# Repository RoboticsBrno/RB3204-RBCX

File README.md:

# RB3204-RBCX

<p align="center">

</p>

RBCX is a universal controller for hobby robots. It is a successor of [RB3201-RBControl](https://github.com/RoboticsBrno/RB3201-RBControl).
It is used in our robot [Robotka](https://robotka.robotickytabor.cz) on [Robo camp 2020](https://robotickytabor.cz).

<div align="center">
  	<td></td>
	<td></td>
</div>

## Features
- 4 DC motors with encoders
- 4 servos with feedback (via ADC)
- 4 LEDs
- buttons with the gamepad interface
- Smart Servo connector
- piezo buzzer
- RTC
- ultra-sonic distance sensor connector
- I2C connectors
- OLED display connector
- accelerometer and gyroscope
- micro USB and USB-C connectors
- battery connector (without charging circuit)

## Hardware
Board is based on `STM32F103VC` microcontroller and `ESP32-DevKitC`.

STM32 is used for motor control and other low-level tasks.
ESP32 is used for high-level tasks like communication with mobile app and sending commands to STM32 via UART.

### [STM32F103VC](https://www.st.com/en/microcontrollers-microprocessors/stm32f103vc.html)

-  72 MHz, 32bit ARM Cortex-M3
-  48 KiB RAM, 256 KiB Flash
-  5x UART, USB
-  Debug support (with ST-Link)
-  Programmable in C++, with FreeRTOS and stm32cube framework, in Platform.io
-  Our [bootloader](https://github.com/RoboticsBrno/sboot_stm32) based on [sboot_stm32](https://github.com/dmitrystu/sboot_stm32).

### [ESP32-DevKitC](https://www.espressif.com/en/products/devkits/esp32-devkitc)

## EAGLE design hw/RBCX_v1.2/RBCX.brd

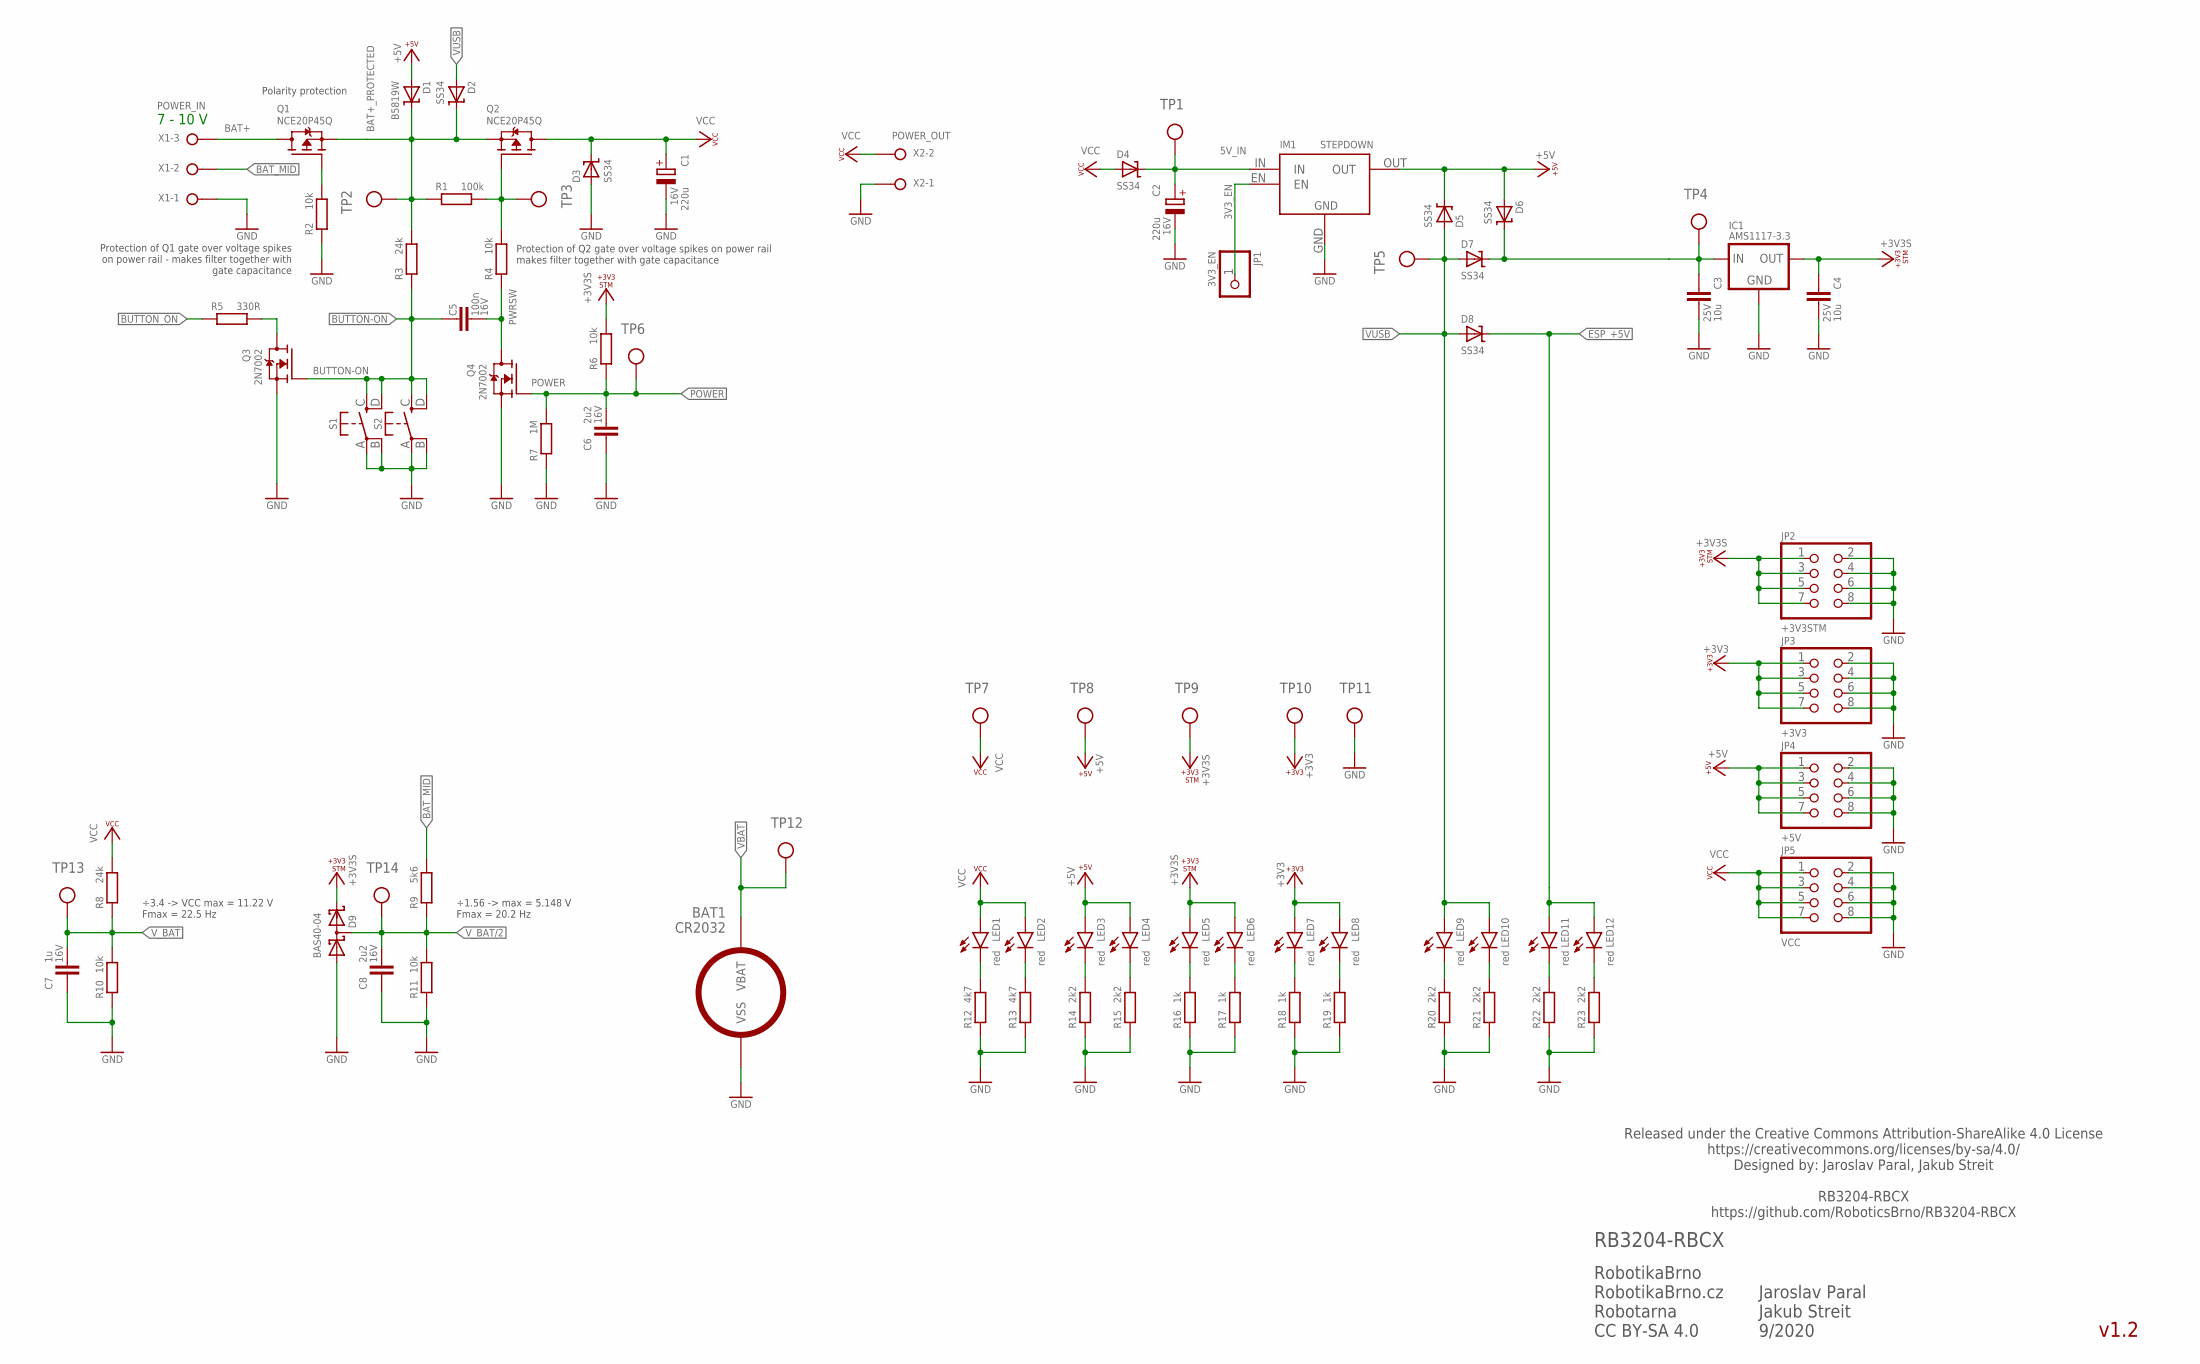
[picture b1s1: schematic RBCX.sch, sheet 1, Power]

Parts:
BAT1: CR2032; SMD-BAT-CR2032-BS-6-1
C1, C2: 220u; E5-10,5; VOLTAGE 16V
C3, C4: 10u; C0805; VOLTAGE 25V
C5: 100n; C0402; VOLTAGE 16V
C6, C8: 2u2; C0603; VOLTAGE 16V
C7: 1u; C0402; VOLTAGE 16V
D1: B5819W; SOD123; LCSC_ID C305445
D2, D3, D4, D5, D6, D7, D8: SS34; SMA
D9: BAS40-04; SOT23
IC1: AMS1117-3.3; SOT223
IM1: STEPDOWN
JP1: 3V3_EN; 1X01
JP2: +3V3STM; 2X04
JP3: +3V3; 2X04
JP4: +5V; 2X04
JP5: VCC; 2X04
LED1, LED2, LED3, LED4, LED5, LED6, LED7, LED8, LED9, LED10, LED11, LED12: red; CHIPLED_0603
Q1, Q2: NCE20P45Q; MLP3.3X3.3_HS; LCSC_ID C193354
Q3, Q4: 2N7002; SOT23; LCSC_ID C8545
R1: 100k; R0402
R2, R4, R6, R10, R11: 10k; R0402
R3, R8: 24k; R0402
R5: 330R; R0402
R7: 1M; R0402
R9: 5k6; R0402
R12, R13: 4k7; R0402
R14, R15, R20, R21, R22, R23: 2k2; R0402
R16, R17, R18, R19: 1k; R0402
S1, S2: TS-1187A-C-C-B; TS-1187A
TP1, TP2, TP3, TP4, TP5, TP6, TP7, TP8, TP9, TP10, TP12, TP13, TP14: TP_06MM; TP_06
TP11: TP_08MM; TP_08
X1: POWER_IN; W237-133
X2: POWER_OUT; W237-132

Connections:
3V3_EN: IM1.EN, JP1.1
3V3_IN: C3.2, D6.C, D7.C, IC1.3 (IN), TP4.P$1
5V_IN: C2.+, D4.C, IM1.IN, TP1.P$1
+3V3: JP3.1, JP3.3, JP3.5, JP3.7, LED7.A, LED8.A, TP10.P$1; also elsewhere on the board
+3V3S: C4.2, D9.2 (C2), IC1.2 (OUT), IC1.4 (OUT), JP2.1, JP2.3, JP2.5, JP2.7, LED5.A, LED6.A, R6.2, TP9.P$1; also elsewhere on the board
+5V: D1.A, D5.C, D6.A, IM1.OUT, JP4.1, JP4.3, JP4.5, JP4.7, LED3.A, LED4.A, TP8.P$1; also elsewhere on the board
BAT+: Q1.5 (D), Q1.6 (D), Q1.7 (D), Q1.8 (D), Q1.9 (D), X1.3
BAT+_PROTECTED: D1.C, D2.C, Q1.1 (S), Q1.2 (S), Q1.3 (S), Q2.1 (S), Q2.2 (S), Q2.3 (S), R1.1, R3.2, TP2.P$1
BAT_MID: R9.2, X1.2
BUTTON-ON: C5.2, Q3.1 (G), R3.1, S1.C (S), S1.D (S1), S2.C (S), S2.D (S1); also elsewhere on the board
BUTTON-ON-LV: Q3.3 (D), R5.2
BUTTON_ON: R5.1; also elsewhere on the board
ESP_+5V: D8.C, LED11.A, LED12.A; also elsewhere on the board
GND: BAT1.VSS, C1.-, C2.-, C3.1, C4.1, C6.2, C7.2, C8.2, D3.A, D9.1 (A1), IC1.1 (GND), IM1.GND, JP2.2, JP2.4, JP2.6, JP2.8, JP3.2, JP3.4, JP3.6, JP3.8, JP4.2, JP4.4, JP4.6, JP4.8, JP5.2, JP5.4, JP5.6, JP5.8, Q3.2 (S), Q4.2 (S), R2.1, R7.1, R10.1, R11.1, R12.1, R13.1, R14.1, R15.1, R16.1, R17.1, R18.1, R19.1, R20.1, R21.1, R22.1, R23.1, S1.A, S1.B (P1), S2.A, S2.B (P1), TP11.P$1, X1.1, X2.1; also elsewhere on the board
POWER: C6.1, Q4.1 (G), R6.1, R7.2, TP6.P$1; also elsewhere on the board
PROT_GATE: Q1.4 (G), R2.2
PWRLED_+3V3: LED7.C, R18.2
PWRLED_+3V3B: LED8.C, R19.2
PWRLED_+3V3S: LED5.C, R16.2
PWRLED_+3V3S_B: LED6.C, R17.2
PWRLED_+5V: LED3.C, R14.2
PWRLED_+5VESP: LED11.C, R22.2
PWRLED_+5VESP_B: LED12.C, R23.2
PWRLED_+5V_B: LED4.C, R15.2
PWRLED_VCC: LED1.C, R12.2
PWRLED_VCC_B: LED2.C, R13.2
PWRLED_VUSB: LED9.C, R20.2
PWRLED_VUSB_B: LED10.C, R21.2
PWRSW: C5.1, Q4.3 (D), R4.1
PWRSW_GATE: Q2.4 (G), R1.2, R4.2, TP3.P$1
VBAT: BAT1.VBAT, TP12.P$1; also elsewhere on the board
VCC: C1.+, D3.C, D4.A, JP5.1, JP5.3, JP5.5, JP5.7, LED1.A, LED2.A, Q2.5 (D), Q2.6 (D), Q2.7 (D), Q2.8 (D), Q2.9 (D), R8.2, TP7.P$1, X2.2; also elsewhere on the board
VUSB: D2.A, D5.A, D7.A, D8.A, LED9.A, LED10.A, TP5.P$1; also elsewhere on the board
V_BAT: C7.1, R8.1, R10.2, TP13.P$1; also elsewhere on the board
V_BAT/2: C8.1, D9.3 (C1A2), R9.1, R11.2, TP14.P$1; also elsewhere on the board

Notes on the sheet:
Polarity protection
÷3.4 -> VCC max = 11.22 V Fmax = 22.5 Hz
v1.2
RobotikaBrno RobotikaBrno.cz Robotarna CC BY-SA 4.0
RB3204-RBCX
Released under the Creative Commons Attribution-ShareAlike 4.0 License https://creativecommons.org/licenses/by-sa/4.0/ Designed by: Jaroslav Paral, Jakub Streit RB3204-RBCX https://github.com/RoboticsBrno/RB3204-RBCX
Jaroslav Paral Jakub Streit 9/2020
÷1.56 -> max = 5.148 V Fmax = 20.2 Hz
Protection of Q1 gate over voltage spikes on power rail - makes filter together with gate capacitance
Protection of Q2 gate over voltage spikes on power rail makes filter together with gate capacitance
7 - 10 V

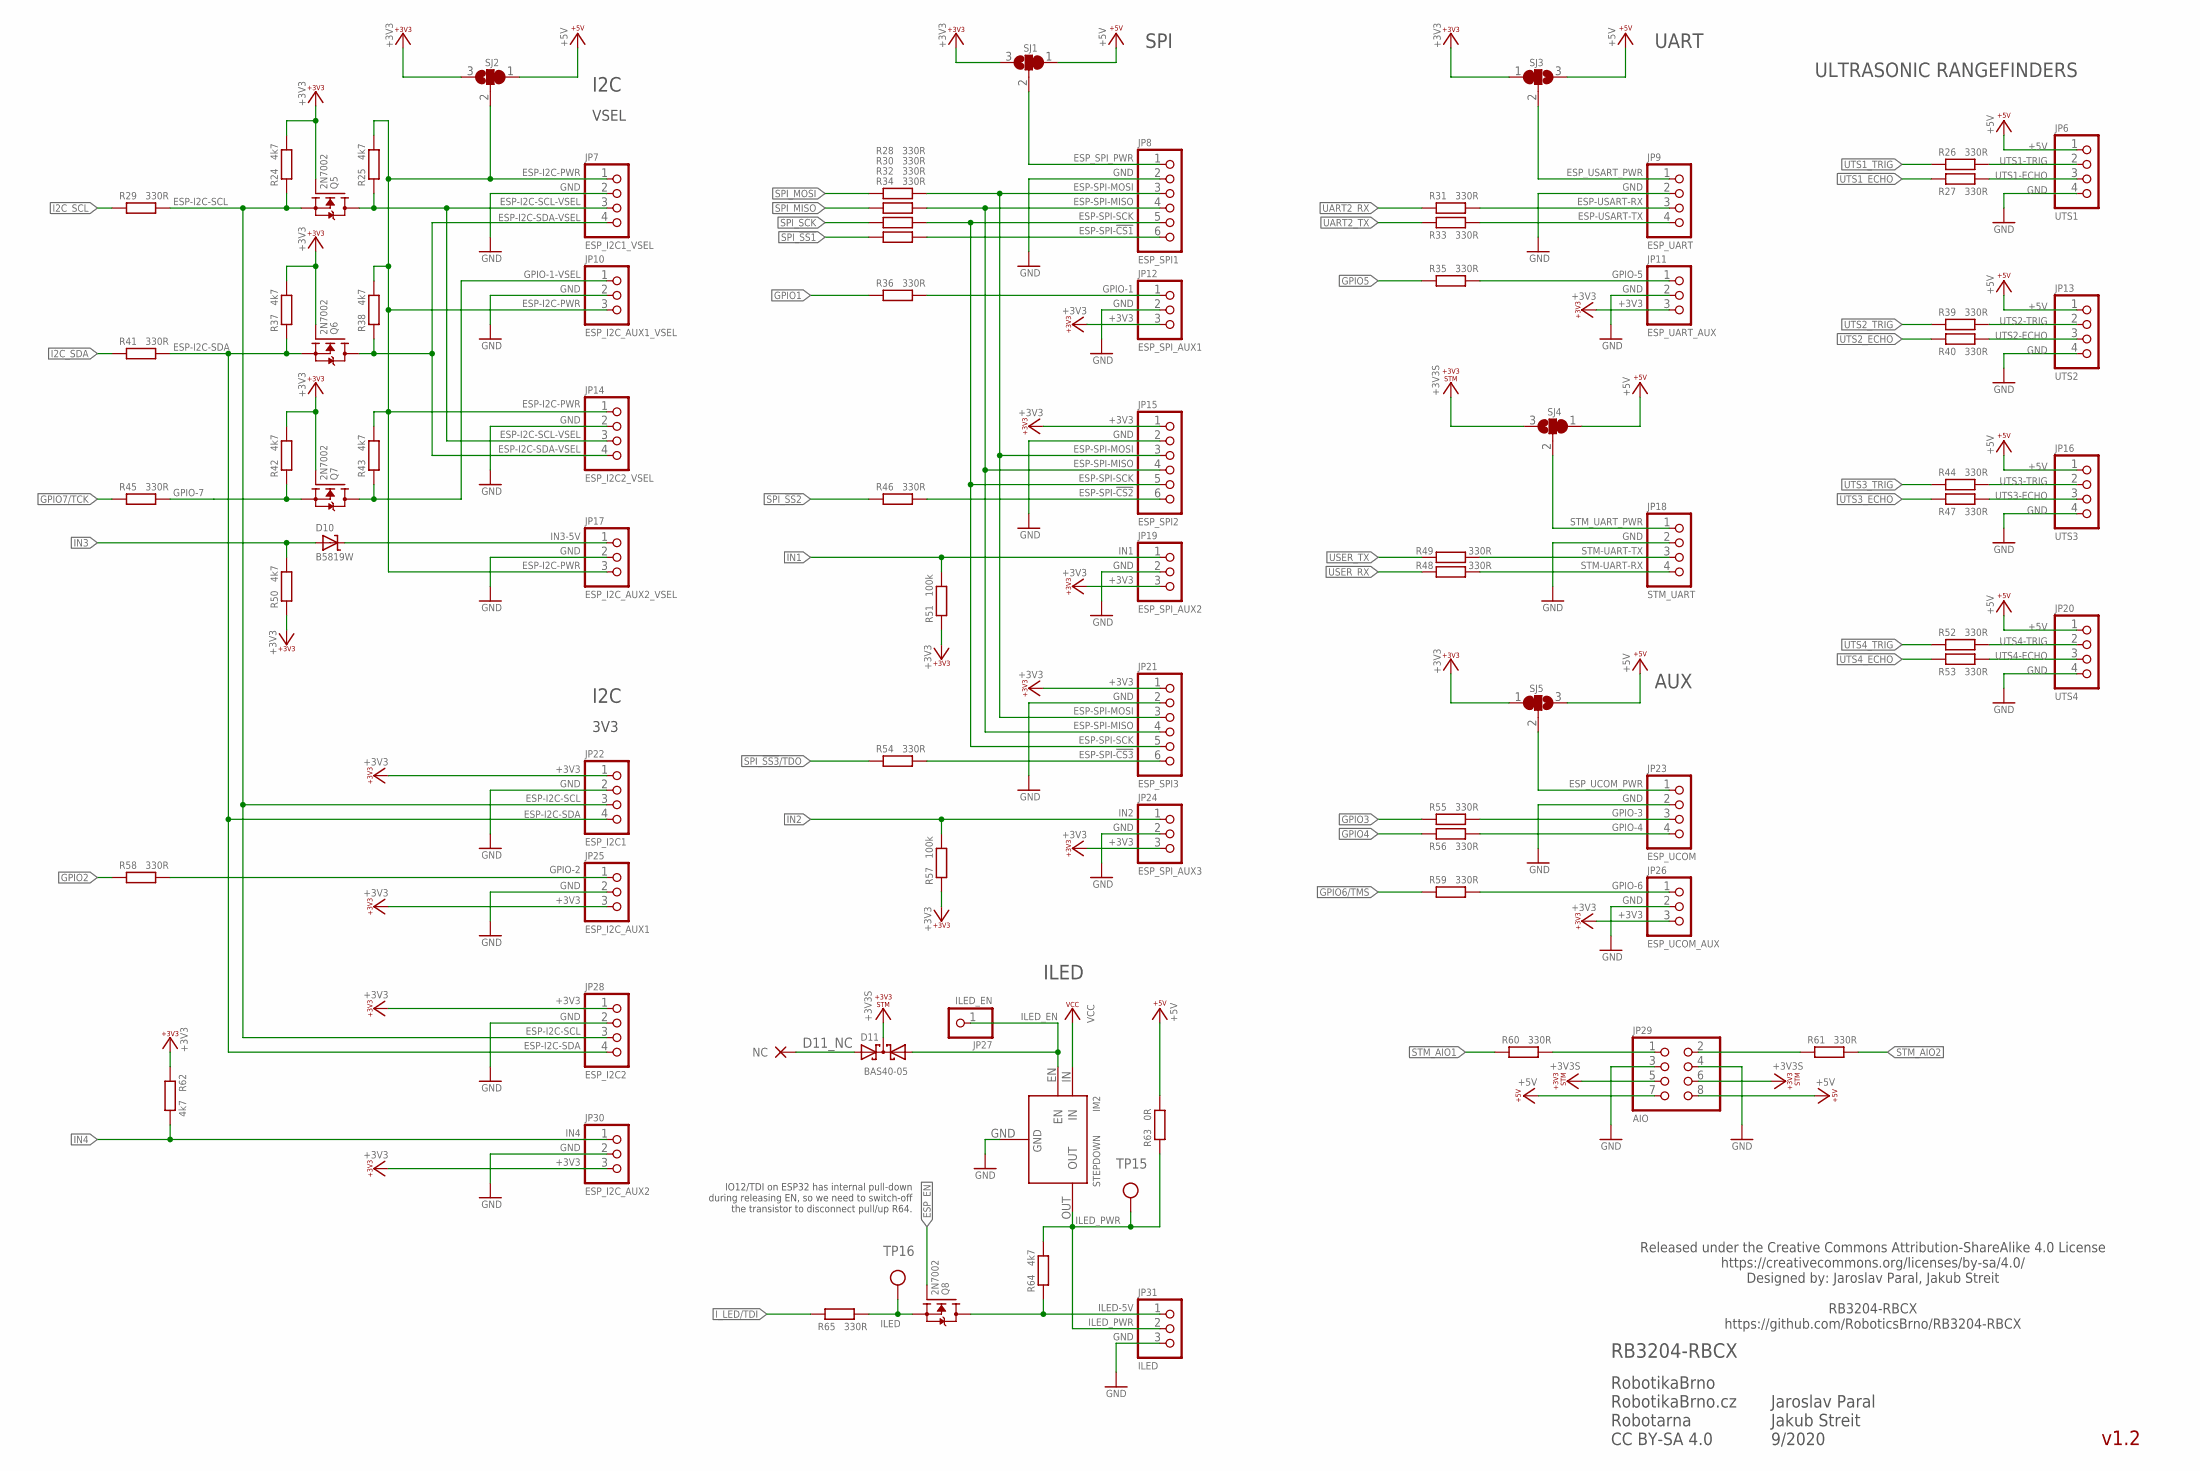
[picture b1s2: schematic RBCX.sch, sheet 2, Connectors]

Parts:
D10: B5819W; SOD123; LCSC_ID C305445
D11: BAS40-05; SOT23
IM2: STEPDOWN
JP6: UTS1; 1X04
JP7: ESP_I2C1_VSEL; 1X04
JP8: ESP_SPI1; 1X06
JP9: ESP_UART; 1X04
JP10: ESP_I2C_AUX1_VSEL; 1X03
JP11: ESP_UART_AUX; 1X03
JP12: ESP_SPI_AUX1; 1X03
JP13: UTS2; 1X04
JP14: ESP_I2C2_VSEL; 1X04
JP15: ESP_SPI2; 1X06
JP16: UTS3; 1X04
JP17: ESP_I2C_AUX2_VSEL; 1X03
JP18: STM_UART; 1X04
JP19: ESP_SPI_AUX2; 1X03
JP20: UTS4; 1X04
JP21: ESP_SPI3; 1X06
JP22: ESP_I2C1; 1X04
JP23: ESP_UCOM; 1X04
JP24: ESP_SPI_AUX3; 1X03
JP25: ESP_I2C_AUX1; 1X03
JP26: ESP_UCOM_AUX; 1X03
JP27: ILED_EN; 1X01
JP28: ESP_I2C2; 1X04
JP29: AIO; 2X04
JP30: ESP_I2C_AUX2; 1X03
JP31: ILED; 1X03
Q5, Q6, Q7, Q8: 2N7002; SOT23; LCSC_ID C8545
R24, R25, R37, R38, R42, R43, R50, R62, R64: 4k7; R0402
R26, R27, R28, R29, R30, R31, R32, R33, R34, R35, R36, R39, R40, R41, R44, R45, R46, R47, R48, R49, R52, R53, R54, R55, R56, R58, R59, R60, R61, R65: 330R; R0402
R51, R57: 100k; R0402
R63: 0R; R1206
SJ1, SJ2, SJ3, SJ4, SJ5: SJ2W_DEFAULT; SJ_2_DEFAULT
TP15, TP16: TP_06MM; TP_06

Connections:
+3V3: JP11.3, JP12.3, JP15.1, JP19.3, JP21.1, JP22.1, JP24.3, JP25.3, JP26.3, JP28.1, JP30.3, Q5.1 (G), Q6.1 (G), Q7.1 (G), R24.2, R37.2, R42.2, R50.1, R51.1, R57.1, R62.1, SJ1.3, SJ2.3, SJ3.1, SJ5.1; also elsewhere on the board
+3V3S: D11.3 (C), JP29.5, JP29.6, SJ4.3; also elsewhere on the board
+5V: JP6.1, JP13.1, JP16.1, JP20.1, JP29.7, JP29.8, R63.2, SJ1.1, SJ2.1, SJ3.3, SJ4.1, SJ5.3; also elsewhere on the board
D11_NC: D11.2 (A2)
ESP-I2C-PWR: JP7.1, JP10.3, JP14.1, JP17.3, R25.2, R38.2, R43.2, SJ2.2
ESP-I2C-SCL: JP22.3, JP28.3, Q5.2 (S), R24.1, R29.2; also elsewhere on the board
ESP-I2C-SCL-VSEL: JP7.3, JP14.3, Q5.3 (D), R25.1
ESP-I2C-SDA: JP22.4, JP28.4, Q6.2 (S), R37.1, R41.2; also elsewhere on the board
ESP-I2C-SDA-VSEL: JP7.4, JP14.4, Q6.3 (D), R38.1
ESP-SPI-!CS1: JP8.6, R34.2
ESP-SPI-!CS2: JP15.6, R46.2
ESP-SPI-!CS3: JP21.6, R54.2
ESP-SPI-MISO: JP8.4, JP15.4, JP21.4, R30.2
ESP-SPI-MOSI: JP8.3, JP15.3, JP21.3, R28.2
ESP-SPI-SCK: JP8.5, JP15.5, JP21.5, R32.2
ESP-USART-RX: JP9.3, R31.2
ESP-USART-TX: JP9.4, R33.2
ESP_EN: Q8.1 (G); also elsewhere on the board
ESP_SPI_PWR: JP8.1, SJ1.2
ESP_UCOM_PWR: JP23.1, SJ5.2
ESP_USART_PWR: JP9.1, SJ3.2
GND: IM2.GND, JP6.4, JP7.2, JP8.2, JP9.2, JP10.2, JP11.2, JP12.2, JP13.4, JP14.2, JP15.2, JP16.4, JP17.2, JP18.2, JP19.2, JP20.4, JP21.2, JP22.2, JP23.2, JP24.2, JP25.2, JP26.2, JP28.2, JP29.3, JP29.4, JP30.2, JP31.3; also elsewhere on the board
GPIO1: R36.1; also elsewhere on the board
GPIO2: R58.1; also elsewhere on the board
GPIO3: R55.1; also elsewhere on the board
GPIO4: R56.1; also elsewhere on the board
GPIO5: R35.1; also elsewhere on the board
GPIO6/TMS: R59.1; also elsewhere on the board
GPIO7/TCK: R45.1; also elsewhere on the board
GPIO-1: JP12.1, R36.2
GPIO-1-VSEL: JP10.1, Q7.3 (D), R43.1
GPIO-2: JP25.1, R58.2; also elsewhere on the board
GPIO-3: JP23.3, R55.2
GPIO-4: JP23.4, R56.2
GPIO-5: JP11.1, R35.2
GPIO-6: JP26.1, R59.2
GPIO-7: Q7.2 (S), R42.1, R45.2
I2C_SCL: R29.1; also elsewhere on the board
I2C_SDA: R41.1; also elsewhere on the board
ILED: Q8.2 (S), R65.2, TP16.P$1
ILED-5V: JP31.1, Q8.3 (D), R64.1; also elsewhere on the board
ILED_EN: D11.1 (A1), IM2.EN, JP27.1
ILED_PWR: IM2.OUT, JP31.2, R63.1, R64.2, TP15.P$1
IN1: JP19.1, R51.2; also elsewhere on the board
IN2: JP24.1, R57.2; also elsewhere on the board
IN3: D10.A, R50.2; also elsewhere on the board
IN3-5V: D10.C, JP17.1
IN4: JP30.1, R62.2; also elsewhere on the board
I_LED/TDI: R65.1; also elsewhere on the board
SPI_!SS1: R34.1; also elsewhere on the board
SPI_!SS2: R46.1; also elsewhere on the board
SPI_!SS3!/TDO: R54.1; also elsewhere on the board
SPI_MISO: R30.1; also elsewhere on the board
SPI_MOSI: R28.1; also elsewhere on the board
SPI_SCK: R32.1; also elsewhere on the board
STM-AIO1: JP29.1, R60.2
STM-AIO2: JP29.2, R61.1
STM-UART-RX: JP18.4, R49.2
STM-UART-TX: JP18.3, R48.2
STM_AIO1: R60.1; also elsewhere on the board
STM_AIO2: R61.2; also elsewhere on the board
STM_UART_PWR: JP18.1, SJ4.2
UART2_RX: R31.1; also elsewhere on the board
UART2_TX: R33.1; also elsewhere on the board
USER_RX: R49.1; also elsewhere on the board
USER_TX: R48.1; also elsewhere on the board
UTS1-ECHO: JP6.3, R27.2
UTS1-TRIG: JP6.2, R26.2
UTS1_ECHO: R27.1; also elsewhere on the board
UTS1_TRIG: R26.1; also elsewhere on the board
UTS2-ECHO: JP13.3, R40.2
UTS2-TRIG: JP13.2, R39.2
UTS2_ECHO: R40.1; also elsewhere on the board
UTS2_TRIG: R39.1; also elsewhere on the board
UTS3-ECHO: JP16.3, R47.2
UTS3-TRIG: JP16.2, R44.2
UTS3_ECHO: R47.1; also elsewhere on the board
UTS3_TRIG: R44.1; also elsewhere on the board
UTS4-ECHO: JP20.3, R53.2
UTS4-TRIG: JP20.2, R52.2
UTS4_ECHO: R53.1; also elsewhere on the board
UTS4_TRIG: R52.1; also elsewhere on the board
VCC: IM2.IN; also elsewhere on the board

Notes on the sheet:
v1.2
RobotikaBrno RobotikaBrno.cz Robotarna CC BY-SA 4.0
RB3204-RBCX
Released under the Creative Commons Attribution-ShareAlike 4.0 License https://creativecommons.org/licenses/by-sa/4.0/ Designed by: Jaroslav Paral, Jakub Streit RB3204-RBCX https://github.com/RoboticsBrno/RB3204-RBCX
Jaroslav Paral Jakub Streit 9/2020
I2C
SPI
UART
VSEL
3V3
ILED
ULTRASONIC RANGEFINDERS
AUX
IO12/TDI on ESP32 has internal pull-down during releasing EN, so we need to switch-off the transistor to disconnect pull/up R64.

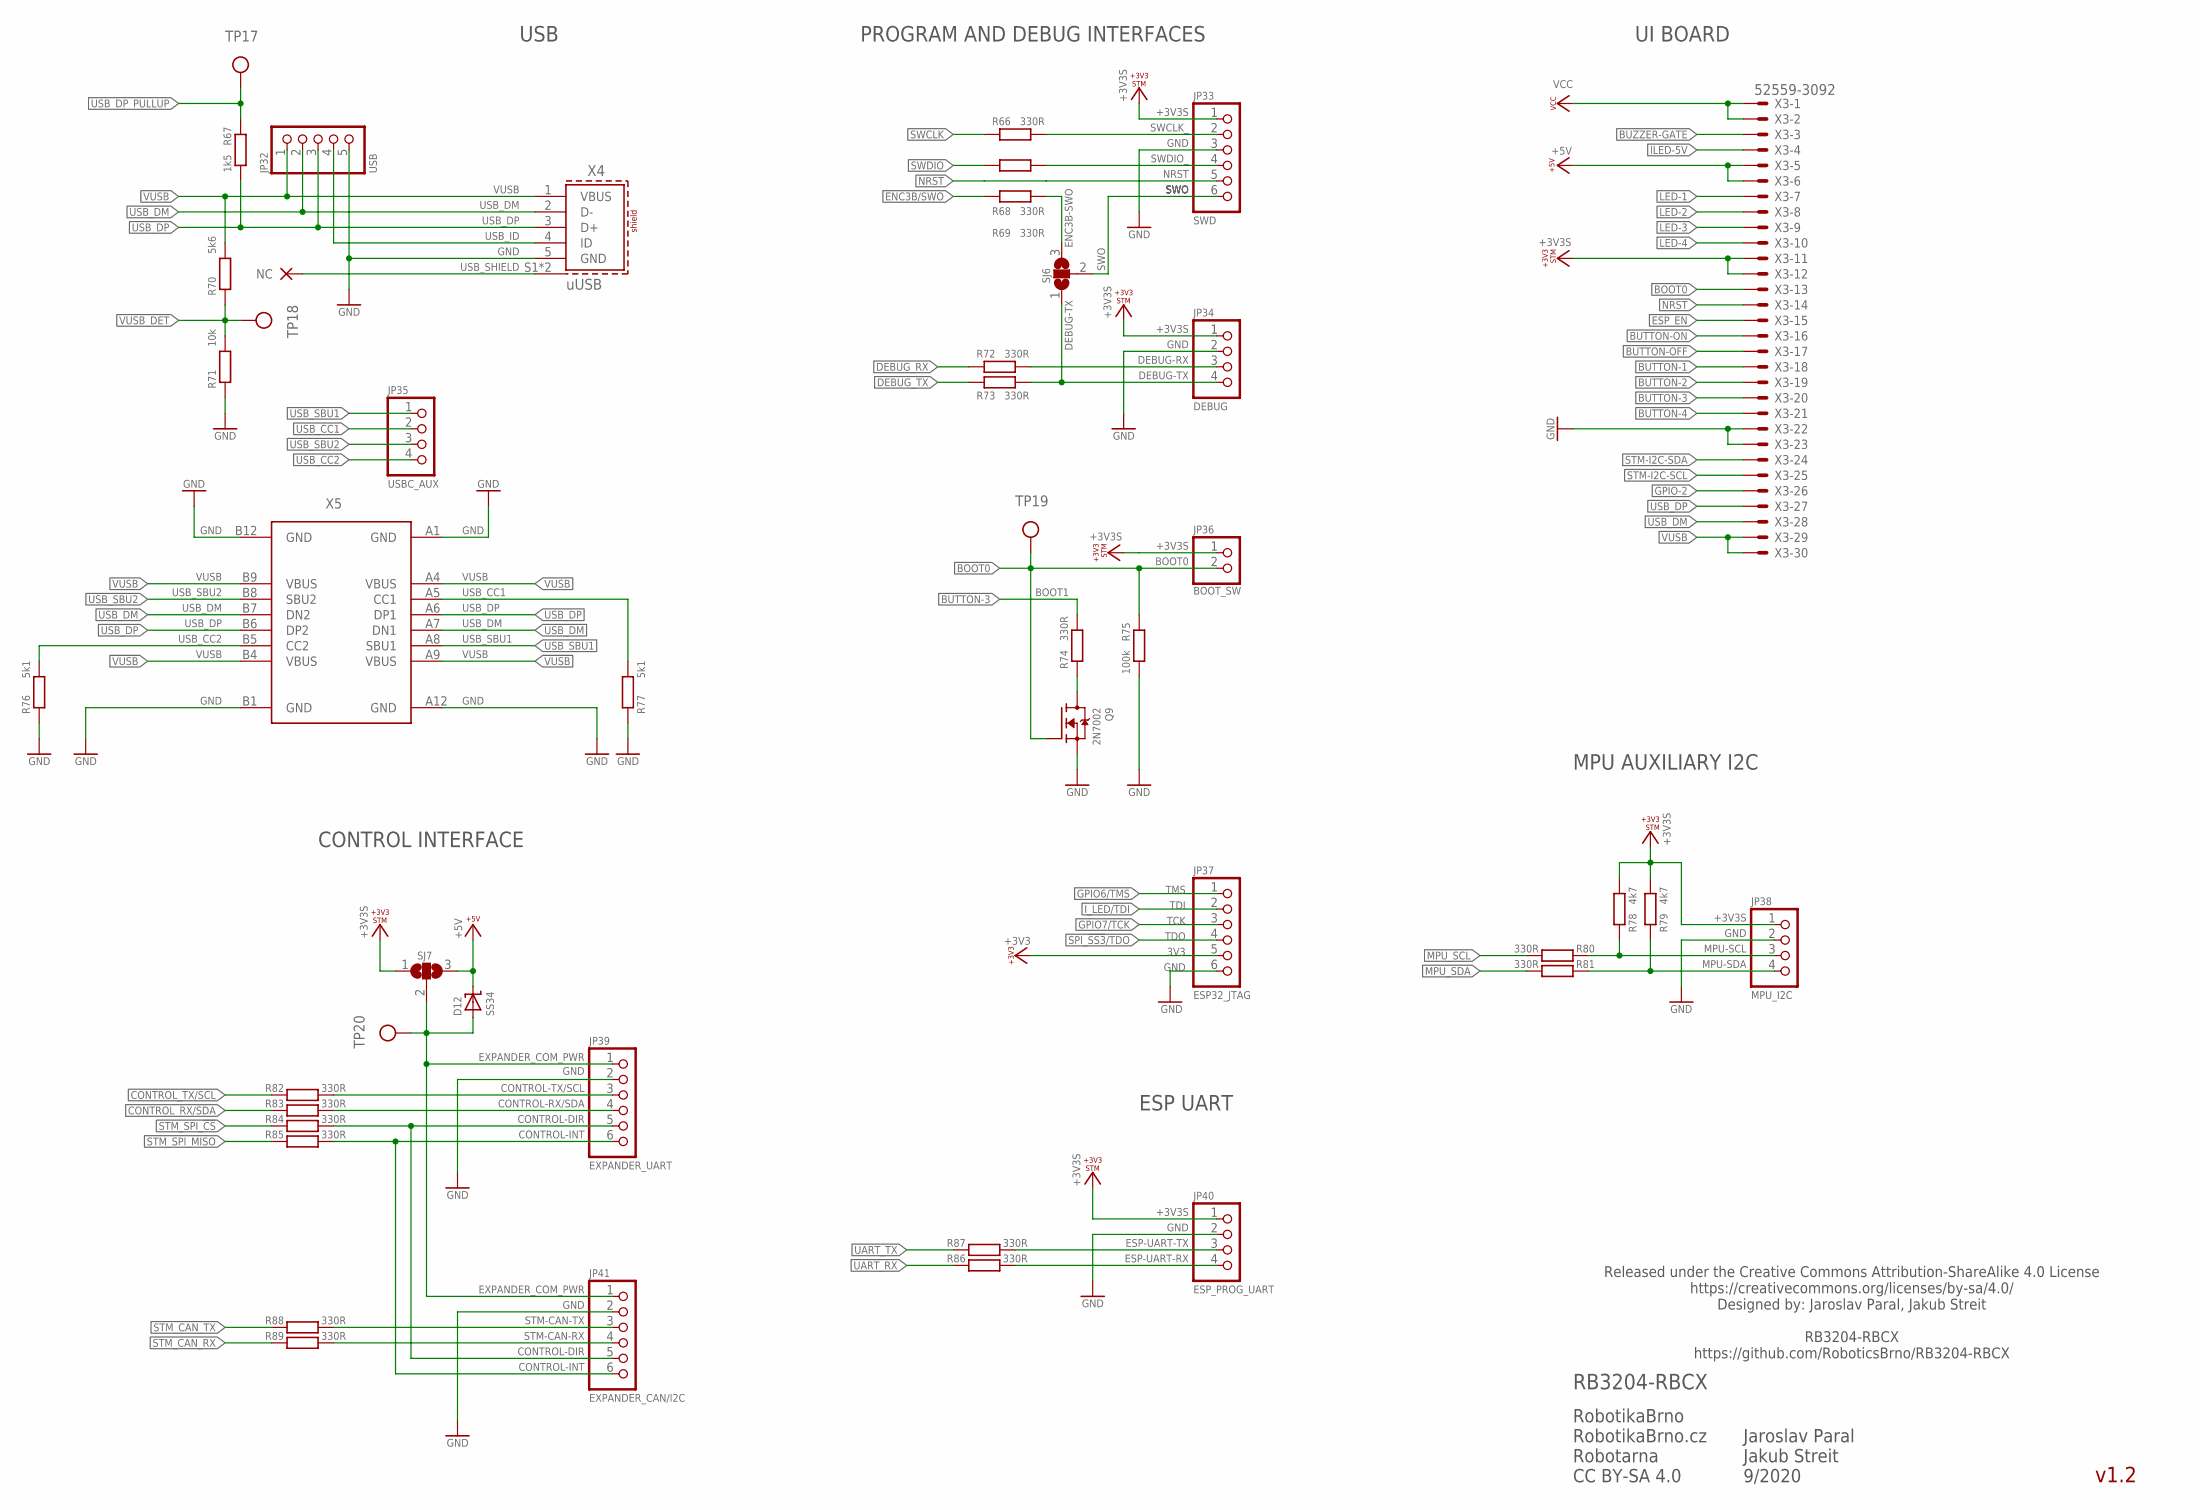
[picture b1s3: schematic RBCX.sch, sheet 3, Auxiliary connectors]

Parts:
D12: SS34; SMA
JP32: USB; 1X05
JP33: SWD; 1X06
JP34: DEBUG; 1X04
JP35: USBC_AUX; 1X04
JP36: BOOT_SW; 1X02
JP37: ESP32_JTAG; 1X06
JP38: MPU_I2C; 1X04
JP39: EXPANDER_UART; 1X06
JP40: ESP_PROG_UART; 1X04
JP41: EXPANDER_CAN/I2C; 1X06
Q9: 2N7002; SOT23; LCSC_ID C8545
R66, R68, R69, R72, R73, R74, R80, R81, R82, R83, R84, R85, R86, R87, R88, R89: 330R; R0402
R67: 1k5; R0402; LCSC_ID C25867
R70: 5k6; R0402
R71: 10k; R0402
R75: 100k; R0402
R76, R77: 5k1; R0402
R78, R79: 4k7; R0402
SJ6, SJ7: SJ2W0603; SJ_2_0603
TP17, TP18, TP19, TP20: TP_06MM; TP_06
X3: 52559-3092
X4: uUSB; 614105150621
X5: USB_C_8PIN; USB_C_VERT_THT_8PIN

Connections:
+3V3: JP37.5; also elsewhere on the board
+3V3S: JP33.1, JP34.1, JP36.1, JP38.1, JP40.1, R78.2, R79.2, SJ7.1, X3.11, X3.12; also elsewhere on the board
+5V: D12.C, SJ7.3, X3.5, X3.6; also elsewhere on the board
BOOT0: JP36.2, Q9.1 (G), R75.1, TP19.P$1, X3.13; also elsewhere on the board
BOOT1_PULL-DOWN: Q9.3 (D), R74.1
BUTTON-1: X3.18; also elsewhere on the board
BUTTON-2: X3.19; also elsewhere on the board
BUTTON-3: R74.2, X3.20; also elsewhere on the board
BUTTON-4: X3.21; also elsewhere on the board
BUTTON-OFF: X3.17; also elsewhere on the board
BUTTON-ON: X3.16; also elsewhere on the board
BUZZER-GATE: X3.3; also elsewhere on the board
CONTROL-DIR: JP39.5, JP41.5, R84.2
CONTROL-INT: JP39.6, JP41.6, R85.2
CONTROL-RX/SDA: JP39.4, R83.2
CONTROL-TX/SCL: JP39.3, R82.2
CONTROL_RX/SDA: R83.1; also elsewhere on the board
CONTROL_TX/SCL: R82.1; also elsewhere on the board
DEBUG-RX: JP34.3, R72.2
DEBUG-TX: JP34.4, R73.2, SJ6.1
DEBUG_RX: R72.1; also elsewhere on the board
DEBUG_TX: R73.1; also elsewhere on the board
ENC3B-SWO: R69.2, SJ6.3
ENC3B/SWO: R69.1; also elsewhere on the board
ESP-UART-RX: JP40.4, R87.2
ESP-UART-TX: JP40.3, R86.2
ESP_EN: X3.15; also elsewhere on the board
EXPANDER_COM_PWR: D12.A, JP39.1, JP41.1, SJ7.2, TP20.P$1
GND: JP32.5, JP33.3, JP34.2, JP37.6, JP38.2, JP39.2, JP40.2, JP41.2, Q9.2 (S), R71.1, R75.2, R76.2, R77.2, X3.22, X3.23, X4.5 (GND), X5.A1 (GND), X5.A12 (GND), X5.B1 (GND), X5.B12 (GND); also elsewhere on the board
GPIO6/TMS: JP37.1; also elsewhere on the board
GPIO7/TCK: JP37.3; also elsewhere on the board
GPIO-2: X3.26; also elsewhere on the board
ILED-5V: X3.4; also elsewhere on the board
I_LED/TDI: JP37.2; also elsewhere on the board
LED-1: X3.7; also elsewhere on the board
LED-2: X3.8; also elsewhere on the board
LED-3: X3.9; also elsewhere on the board
LED-4: X3.10; also elsewhere on the board
MPU-SCL: JP38.3, R78.1, R80.1
MPU-SDA: JP38.4, R79.1, R81.1
MPU_SCL: R80.2; also elsewhere on the board
MPU_SDA: R81.2; also elsewhere on the board
NRST: JP33.5, X3.14; also elsewhere on the board
SPI_!SS3!/TDO: JP37.4; also elsewhere on the board
STM-CAN-RX: JP41.4, R89.2
STM-CAN-TX: JP41.3, R88.2
STM-I2C-SCL: X3.25; also elsewhere on the board
STM-I2C-SDA: X3.24; also elsewhere on the board
STM_CAN_RX: R89.1; also elsewhere on the board
STM_CAN_TX: R88.1; also elsewhere on the board
STM_SPI_!CS: R84.1; also elsewhere on the board
STM_SPI_MISO: R85.1; also elsewhere on the board
SWCLK: R66.1; also elsewhere on the board
SWCLK_: JP33.2, R66.2
SWDIO: R68.1; also elsewhere on the board
SWDIO_: JP33.4, R68.2
SWO: JP33.6, SJ6.2
UART_RX: R87.1; also elsewhere on the board
UART_TX: R86.1; also elsewhere on the board
USB_CC1: JP35.2, R77.1, X5.A5 (CC1)
USB_CC2: JP35.4, R76.1, X5.B5 (CC2)
USB_DM: JP32.2, X3.28, X4.2 (D-), X5.A7 (DN1), X5.B7 (DN2); also elsewhere on the board
USB_DP: JP32.3, R67.2, X3.27, X4.3 (D+), X5.A6 (DP1), X5.B6 (DP2); also elsewhere on the board
USB_DP_PULLUP: R67.1, TP17.P$1; also elsewhere on the board
USB_ID: JP32.4, X4.4 (ID)
USB_SBU1: JP35.1, X5.A8 (SBU1)
USB_SBU2: JP35.3, X5.B8 (SBU2)
USB_SHIELD: X4.S1 (SHIELD), X4.S2 (SHIELD)
VCC: X3.1, X3.2; also elsewhere on the board
VUSB: JP32.1, R70.2, X3.29, X3.30, X4.1 (VBUS), X5.A4 (VBUS), X5.A9 (VBUS), X5.B4 (VBUS), X5.B9 (VBUS); also elsewhere on the board
VUSB_DET: R70.1, R71.2, TP18.P$1; also elsewhere on the board

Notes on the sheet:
v1.2
RobotikaBrno RobotikaBrno.cz Robotarna CC BY-SA 4.0
RB3204-RBCX
Released under the Creative Commons Attribution-ShareAlike 4.0 License https://creativecommons.org/licenses/by-sa/4.0/ Designed by: Jaroslav Paral, Jakub Streit RB3204-RBCX https://github.com/RoboticsBrno/RB3204-RBCX
Jaroslav Paral Jakub Streit 9/2020
PROGRAM AND DEBUG INTERFACES
USB
ESP UART
UI BOARD
TDI
TMS
TCK
TDO
3V3
GND
BOOT1
CONTROL INTERFACE
MPU AUXILIARY I2C

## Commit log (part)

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2020-04-07 Add the CDC loopback demo, adjusted
2020-04-08 MainBoardBRD: change top side SMD parts footprint according IPC-7351 (using Library Expert Pro (2019.7) )
2020-04-11 Remove HID thing from USB
2020-04-12 Add bsp.hpp, add USART WIP
2020-04-13 Add DMA-enabled transmission for USART1
2020-04-15 MainBoard: 4 layers, motors connector, DRV8833, libraries
    - set 4 layers stack + change DRC setting about same signals, the rest is still same (possible place
    for improvements due to 4 layers stack and https://jlcpcb.com/capabilities/Capabilities)
    - motors connectors - remove terminal blocks, replace pinheads with JST-PH6 (2mm x 6 pins)
    - DRV8833
    - improve `DRV8833.lbr` library - fix thermal GND pad under the package
    - reroute on DPS and add thermal VIAs according http://www.ti.com/lit/an/slma004b/slma004b.pdf
2020-04-16 Fix fifo overrun
2020-04-18 MainBoard: Change power circuit to make ON button connected to GND
2020-04-18 MainBoard: Invalidate parts.xlsx
2020-04-18 MainBoardBRD: routing power - VCC, 5V, servo, DRV8833
2020-04-19 Add working cdc_uart_tunnel.cpp
2020-04-20 Fix PMA buffer overrun
2020-04-23 MainBoardBRD: routing
2020-04-24 Use polling for both CDC OUT and IN
2020-04-24 Increase primary UART RX ring buf size
2020-04-25 Apply formatting
2020-04-26 Fixup string descriptors
2020-04-26 Fix function name convention
2020-04-26 Fix pinInit()
2020-04-29 fw: add TravisCI config for rbcx-coprocessor project
2020-04-30 MainBoard: Add leds and uUSB to bottom side, move the leftmost pinheads far from the board edge, fix DRC error in DRV8833 library, swap position of servos and motors + power connectors
2020-05-02 MainBoard: Add power LEDs for VUSB and +5V_ESP and secondary power LEDS for +3v3S and VCC
2020-05-03 Fix function name convention
    Fix function name convention
    Fix method naming convention
    Fix pinInit()
    Fix cdcLinkPoll name
2020-05-03 Add basic docs
2020-05-05 TravisCI: change from Python 2.7 to 3.7
2020-05-05 Add doc for ByteFifo
2020-05-06 MainBoard: Swap IN4A and IN4B, routed motors + servos
2020-05-06 MainBoard: Fix USB connectors packages, add Design block backup file extensions to gitignore
2020-05-06 MainBoard: Mirror motor connectors (to the bottom side) and swap signals to keep previous routing
2020-05-06 MainBoard: Routing (coprocessor power), remove one output capacitor from LDO - shared with STM
2020-05-07 MainBoardBRD: Fix DRC errors
2020-05-07 MainBoardSCH: Reorder sheets and renumber parts
2020-05-07 MainBoardBRD: Mirror servos step-down enable pin
2020-05-07 MainBoardBRD: Add basic topside silkscreen
2020-05-08 MainBoardBRD: improve top and bottom silkscreen
2020-05-09 ele/hw: clean and refactor project structure
    - rename folder `ele` to `hw`
    - remove folder `MainBoard`
    - to folder `hw` add folders `lib`,`configuration` and `designBlock`
    - rename `RBCX-MainBoard{.brd/.sch}` to `RBCX{.brd/.sch}`
2020-05-11 hw: Add default V resistors, fix polygon Q1, prepare manufacturing data
    - add 0R resistors as default voltage selector for SJx
    - improve size of polygon for Q1 due to better cooling
    - prepare manufacturing data
    - renumber parts in schema
    - create `parts_SMT.xlsx` file with updated data
    - add CAM processor configuration
2020-05-11 MainBoardBRD: Add placeholder text for JLCPCB order number
2020-05-11 MainBoard: Swap PWM3A and PWM3B to maintain consistency
2020-05-11 MainBoardBRD: Remove SolderPaste from jumpers
2020-05-11 hwBRD: Improve silkscreen
    - silkscreen: fix motors JST connectors VCC/GND, update communication connectors
    - modify silkscreen of ESP32-DEVKITC in library `esp32.lbr`
2020-05-12 Unify clocksInit()
2020-05-13 Revert DRV8833-PWM-test
2020-05-15 Add control frame loopback
2020-05-17 Fix frame buffer size, hide ControlLink symbols from linker
2020-05-19 hw: clean `parts_SMT.xlsx`
2020-05-19 hw: create folder `RBCX_v1.0` with manufactured Eagle PCB files
2020-05-19 hwBRD: Fix R47 misplacement
2020-05-19 hwBRD: Fix SPI_SS3 and IN3 overlap
2020-05-21 hw_test: copy actual firmware from master
2020-05-22 hw_test: rename UARTs, add UARTs and their pins, systick interrupt blinks LED1 (not tested), add ST-LINK to platformio.ini
2020-05-23 fw: format whole code base with our `.clang-format`
    - add limit of 80 character per line to `.clang-format` file
    - format our files
    - src\*{.c/.cpp}
    - include\*{.h/.hpp}
    - add `formatOnSave` to VSCode setting
2020-05-23 Use encodeWithHeader
2020-05-23 Use MaxFrameSize instead of 257
2020-05-24 hw_test: fix tunnel spelling
2020-05-24 hw_test: USB test - redirected to debug USART, because of presence of DMA
2020-05-24 Format some files again after merge with master
2020-05-30 hw_test: buzzer test
2020-05-30 hw_test: RTC test - remove output pulse and add synchronization delay before printing
2020-06-02 hw_test: PWM test
2020-06-02 hw_test: PWM test: add explanation
2020-06-02 hw_test: fix broken Bsp.hpp from PWM test, add encoders
2020-06-03 hw_test: fix AFIO_MAPR write-only bits SWJ_CFG issue. DO NOT USE LL_GPIO_AF_*Remap* FUNCTIONS! Use LL_GPIO_AF_Remap instead.
2020-06-03 Add FreeRTOS files
2020-06-03 Remove forgotten prototype
2020-06-06 hw: update pinhead library
    - update pinhead library in RBCX design and modify the XML in `RBCX{.brp/.sch}` for correct import to KiCad
2020-06-06 Fix button order
2020-06-07 Add C_Cpp.default.includePath to VSCode settings.json
2020-06-07 Add .gitignore
2020-06-07 Fix all warnings
2020-06-07 Add servo control
2020-06-07 Fix missing break
2020-06-07 Simplify pwm computation, enable servo disable
2020-06-11 Implement DebugLink, some refactoring
2020-06-11 hw: apply pinout to the schematic
2020-06-11 hw: fix power circuit capacitors value
2020-06-11 hw: remove resistor between STM and ESP enable
2020-06-12 hw: add middle battery voltage (with overvoltage protection) to the power input terminal block (replaced by 3-pin)
2020-06-12 Remove v1.1 BSP preparation
2020-06-13 Re-implement _exit to handle abort()
2020-06-13 WIP: Add ultrasound
2020-06-14 Fix CdcUartTunnel, implement ESP32 boot sequences
2020-06-15 hw: fix DRV8833 packages (stop mask and orientation)
2020-06-15 hw: swap button 3 and 4, routing
2020-06-15 Refactor the Esp32Manager to emulate the ESP32 devkit more closely
2020-06-15 DebugLink fixups
2020-06-15 Switch ControlLink speed to 921600
2020-06-16 hw: routing
2020-06-16 Do not call DeInit in pinInit by default (fixes powering on)
2020-06-17 hw: routed
2020-06-17 hw: fix polygons and GND testpoint
2020-06-17 hw: minor fixes
2020-06-17 hw: move components away from pinheads
2020-06-17 hw: jumpers modified to match 0603 resistors
2020-06-17 hw: fix value of R74
2020-06-17 Use uintptr_t, log status queue oflow
2020-06-18 hw: move some resistors, because of silkscreen
2020-06-19 hw: update and fix silkscreens
    - fix position of labels
    - add testpoint labels
    - improve groups of text (separate columns in text labels)
    - add label for capacitors polarity
    - change layer from `tDocu` to `Document` for label in library `switch-omron.lbr`
2020-06-20 Add motor PWM control by @cednik
2020-06-21 hw: change outline layer of display modules
    - `diy-modules.lbr` - change outline layer from `tPlace` to `Document`
    - footprint `DISPLAY-OLED-128X32`
    - footprint `DISPLAY-OLED-128X64-I2C_W-HOLES`
2020-06-21 Add setBrake
2020-06-22 hw: fix position of origin in default jumper footprint
    - library `jumper.lbr` - `SJ2W_DEFAULT` - fix position of origin
    - update `RBCX.brd`
2020-06-22 hw: remove bottom mask under DRV8833s center pad
2020-06-22 hw: change size of holes for USBC connector
    - library `USB.lbr`
    - footprint `USB_C_8PIN` - change holes size from 0.35 mm to 0.30 mm to fit JLCPCB requirements
2020-06-22 Implement power off button
2020-06-24 Implement Esp32 watchdog
2020-06-24 FW test: add ADC, battery ADCy o working
2020-06-26 Use 100Hz motor loop, initialize pid
2020-06-27 Make motor loop more isochronous, use periodic dither, adjust default PID
2020-06-28 Properly init EN edge in Esp32Manager on startup
2020-06-29 Add motor state switching, tune back PID
2020-07-01 Remove DEBUG from motor loop
2020-07-03 Handle missing fw_ version tag
2020-07-05 hw: Release/manufacture version 1.1
    Summary:
    - fix USB-C connector - footprint `USB_C_8PIN` - change holes size from 0.35 mm to 0.30 mm to fit JLCPCB requirements
    - add USB-C auxiliary signals connector and soldering pads around USB connectors for better fixation
    - remove bottom mask and fix stop mask under DRV8833s centre pad
    - modify jumpers to match 0603 resistors size
    - fix position of origin in default jumper footprint for correct SMT
2020-07-05 Fix Queue and MessageBuffer wrapper's ISR yield handling
2020-07-05 Expand main task stack to 3KB to be safe
2020-07-05 Implement a softReset(); method
2020-07-06 Add commands to set motor power, velocity
2020-07-06 Use STM32's uid as serial number for the USB link
2020-07-06 Use INT16_MAX
2020-07-06 Simplify dither logic
2020-07-06 Add MutexWrapper and scoped_lock usage
2020-07-06 Simplify Regulator
2020-07-07 Don't give mutex on creation
2020-07-08 Add datasheets
2020-07-08 hw: remove old "parts (not updated).xlsx"
2020-07-08 doc: add CZ asembly manual for robot Robotka
2020-07-09 Handle USB events in IRQ rather than polling
    * The main loop is too slow for Windows drivers due to control
    messages decoding taking too long.
2020-07-10 Update BSP for v1.1, add more debug commands
    Closes #43
2020-07-11 Support building and flashing via sboot
    Updates #33
2020-07-11 Auto-reset RBCX into DFU on sboot upload
2020-07-11 Print detected version during build
2020-07-11 Add more delay for the debug uart btn check
2020-07-11 Fix post_dfu.py on Windows
2020-07-11 Add watchdog inhibit with debugger attached
2020-07-13 Add ENC filter
2020-07-13 Add homing/clearing of current position
2020-07-13 Fix member initialization in Motor
2020-07-13 Set target velocity=0 at position achieved instead of turning off
2020-07-13 Reinitialize motor to defaults at softreset, add MotorStat transaction
2020-07-15 Use better ramping logic
2020-07-15 Use sqrti
2020-09-19 hw: change version to v1.2
2020-09-19 hw: disconnect 3V3_EN and D11 (this connection prevents main step-down IM1 from startup)
2020-09-20 hw: update resistors R20-R23 value in parts_SMT.xlsx
2020-10-10 hw: add place for owner name
2020-10-11 hw: fixed iLed silkscreen
2020-10-12 hw: clean tNames and bNames
2020-10-12 hw: add pull-up resistors to encoders
2020-10-12 hw: add assembly variants
2020-10-12 hw: add D1 attributes
2020-10-12 hw: v1.2 snapshot
2021-04-05 Start LSE oscillator at clocks startup
2021-04-06 Enable RTC
2021-04-19 Revert velocity ramping motor changes
    They did not work well in real-world testing and we want the master
    to be useable.
    This reverts commit ca02e360475b70f186cf4639121ef47abeeff4ba.
    This reverts commit 5b80842b56ccd478ef0caa50ece7596251d0460a.
    This reverts commit d5262ff970676f4caf6ee55bf52c5202b1f619d8.
2021-04-19 Add RTC dispatch and alarm logic
2021-04-26 Init I2C
2021-04-26 I2C tests
2021-04-27 I2c ready to use
2021-04-30 I2c add CoprocStat for ESP
2021-04-30 Fix broken inclide
2021-05-01 Add OLED I2C driver
2021-05-02 Fix I2C devAddress
2021-05-02 OLED read requests from ESP
2021-05-02 Remove 'primary' uart historical mention
2021-05-05 Add full OLED support trought ESP
2021-05-08 MPU add basic commands for ESP
2021-05-11 Add nonblocking I2C experiment
2021-05-12 Fix include in Mpu header
2021-05-15 I2c add getCurrentTask - taskNotify and I2c mutex
2021-05-16 Remove HW 1.0 from CI
2021-07-22 Make i2c asynchronous
2021-07-23 Fix ESP reset by change i2c queue timeout, add i2c reset
2021-07-26 Add i2c error message
2021-07-26 Fix coproc link
2021-07-27 Fix MPU timer reinit
2022-10-13 Bump coproc comm for power coupling
2022-10-17 Simplify power coupling logic
2022-11-21 Remove stepdowns, Micro-USB; fixup region names
2023-02-08 Work in progress
2023-02-12 Labels on PCB
2023-02-12 Readme
2023-02-12 Production files
2023-02-15 Solder mask clearance
2023-02-18 Protective resistors for I2C on connectors
2023-02-27 Kuba issues - PCB
2023-03-04 Few small things
2023-03-25 Add images, fix doc
2023-03-25 Add open_in_new_tab.js
2023-03-26 Add views badges
2023-03-31 USB-DET level shifter
2023-05-02 Add support for CoprocStartup and EspWatchdogSettings messages
2023-05-30 Simplify the smart servo tunnel

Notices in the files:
parts and their libraries:
esp32: Creative Commons Attribution-ShareAlike 4.0 International
diy-modules: Released under the Creative Commons Attribution 4.0 International License: http://creativecommons.org/licenses/by/4.0
